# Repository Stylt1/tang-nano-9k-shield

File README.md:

<div align="center">

# Tang Nano 9K Shield

**A retro‑computing & I/O expansion board for the Sipeed Tang Nano 9K FPGA**

VGA · dual PS/2 · RP2040 co‑processor · USB‑C · Pmod · 16 DIP switches · SPI / I²C headers

</div>

---

## Table of contents

- [Overview](#overview)
- [Features](#features)
- [Gallery](#gallery)
- [Block diagram](#block-diagram)
- [Schematic](#schematic)
- [Hardware](#hardware)
  - [Power](#power)
  - [Video – VGA](#video--vga)
  - [Input – PS/2](#input--ps2)
  - [RP2040 co‑processor](#rp2040-co-processor)
  - [Pmod](#pmod)
  - [Headers](#headers)
- [Pin mapping](#pin-mapping)
- [PCB](#pcb)
  - [Layer stack](#layer-stack)
- [Getting started](#getting-started)
- [Repository structure](#repository-structure)
- [Status](#status)
- [License](#license)

---

## Overview

The **Tang Nano 9K Shield** turns the tiny Sipeed Tang Nano 9K into a small,
self‑contained retro computer / FPGA playground. The FPGA drives a **VGA monitor**
and reads two **PS/2 devices** (keyboard + mouse). An on‑board **RP2040** acts as a
co‑processor: it talks to the FPGA over SPI, reads **16 DIP switches**, and exposes
**USB‑C**, **I²C** and **SPI** to the outside world. A level‑shifted **Pmod** port lets
you plug in standard Digilent‑compatible modules.

The board runs from a **7.5–15 V DC barrel jack**, from **USB‑C**, or from the
**Tang Nano’s own USB**, all OR‑ed together with Schottky diodes.

## Features

| | |
|---|---|
| 🖥️ **VGA output** | DE‑15 connector, 4‑bit‑per‑channel resistor DAC (4096 colours), HSYNC / VSYNC |
| ⌨️ **2 × PS/2** | Stacked mini‑DIN 6 (keyboard + mouse), 5 V ↔ 3.3 V bidirectional level shifting |
| 🧠 **RP2040 co‑processor** | 133 MHz dual Cortex‑M0+, 4 MB QSPI flash, 12 MHz crystal, BOOT / RESET jumpers |
| 🔌 **USB‑C** | RP2040 native USB with ESD protection, VBUS detection and a switchable 5 V output (USB host mode) |
| 🎛️ **16 DIP switches** | 2 × 8‑way slide switches with pull‑ups, read by the RP2040 |
| 🧩 **Pmod port** | 2 × 6 right‑angle socket, 8 lines translated 1.8 V ↔ 3.3 V (TXS0108E) |
| 📡 **Expansion** | 7‑pin SPI header (CS + INT) and 4‑pin I²C header (4.7 kΩ pull‑ups) |
| ⚡ **Flexible power** | 7.5–15 V DC jack → 5 V synchronous buck, USB‑C, or Tang USB; on‑board 3.3 V and 1.8 V LDOs |
| 💡 **Status LEDs** | 5 V and 3.3 V power indicators |

## Gallery

### Renders

| Top | Bottom |
|:---:|:---:|
|  |  |
|  |  |

### KiCad 3D views

| Top | Bottom |
|:---:|:---:|
|  |  |

| VGA side | PS/2 side |
|:---:|:---:|
|  |  |

| DIP switches | Power & Pmod |
|:---:|:---:|
|  |  |

### Copper layers

| F.Cu – top · GND pour · main signals | In1.Cu – inner 1 · GND reference plane |
|:---:|:---:|
|  |  |

| In2.Cu – inner 2 · 3V3 pour · power & tertiary signals | B.Cu – bottom · GND pour · secondary signals |
|:---:|:---:|
|  |  |

<sub>Renders: KiCad 3D raytracer composited onto CC0 surface textures from <a href="https://polyhaven.com">Poly Haven</a>.</sub>

## Block diagram

<details>
<summary><b>Text version</b></summary>

```text
                    ┌──────────────────────────────┐
  DC 7.5–15 V ──►   │  TPS563201 buck  →  5V_BUCK  │──┐
                    └──────────────────────────────┘  │
  USB‑C VBUS ─────────────────────────────────────────┼──► 5 V rail ──► TLV75533 ─► 3V3 ──► TLV75518 ─► 1V8
  Tang 5 V   ◄────────────────────────────────────────┘    (Schottky OR‑ing)

 ┌───────────────────────┐   SPI (CS1 / INT1)   ┌─────────────────────────┐
 │                       │◄────────────────────►│        RP2040           │
 │   Tang Nano 9K        │                      │  W25Q32 flash, 12 MHz   │
 │   (Gowin GW1NR‑9)     │                      │                         │
 │                       │── RGB 4:4:4 + sync ──► VGA (DE‑15)              ├──► USB‑C (ESD, VBUS switch)
 │                       │◄─ 2 × CLK/DATA ──────► BSS138 ──► PS/2 × 2       ├──► 16 × DIP switch
 │                       │◄─ 8 lines @1.8 V ────► TXS0108E ──► Pmod (3.3 V)├──► I²C header
 │                       │◄─ SPI (CS2 / INT2) ──► SPI header               │
 └───────────────────────┘                      └─────────────────────────┘
```

</details>

Source: [`hardware/block_diagram.kicad_sch`](hardware/block_diagram.kicad_sch)

## Schematic

📄 Full-resolution PDF: [`docs/schematic.pdf`](docs/schematic.pdf) · Source: [`hardware/tang-nano-9k-shield.kicad_sch`](hardware/tang-nano-9k-shield.kicad_sch)

## Hardware

### Power

| Rail | Source | Part | Notes |
|---|---|---|---|
| **VIN** | DC barrel jack, **7.5–15 V, centre positive** | SS14 | Reverse‑polarity protection |
| **5V_BUCK** | VIN | TPS563201 | Synchronous buck, set to 5.07 V (56 k / 10 k divider) |
| **5V** | 5V_BUCK / USB‑C / Tang 5 V | 4 × SS14 | Diode OR‑ing of all three sources |
| **3V3** | 5V | TLV75533 | RP2040, logic, pull‑ups, Pmod VCC |
| **1V8** | 3V3 | TLV75518 | Side A of the Pmod level shifter (FPGA bank 3) |

> [!NOTE]
> The Tang Nano’s own 3.3 V pin is intentionally **not** used. The shield generates its own 3.3 V.

### Video – VGA

- 12 FPGA outputs → 4‑bit binary‑weighted resistor DAC per channel
  (**510 Ω / 1 kΩ / 2 kΩ / 3.9 kΩ**) → ~0.7 V full scale into the monitor’s 75 Ω.
- HSYNC / VSYNC through 100 Ω series resistors.
- 4096 colours (RGB 4:4:4).

### Input – PS/2

- Stacked dual mini‑DIN 6: **top = mouse (purple)**, **bottom = keyboard (green)**.
- Bidirectional open‑drain level shifting with **BSS138** MOSFETs (5 V ↔ 3.3 V),
  4.7 kΩ pull‑ups on both sides, 330 Ω series resistors on the connector side.

### RP2040 co‑processor

- RP2040 + **W25Q32JV** 4 MB QSPI flash + **12 MHz** crystal (Raspberry Pi reference design).
- **BOOT** and **RESET** solder jumpers for entering the USB bootloader.
- **USB‑C**: USBLC6‑2SC6 ESD protection, 27 Ω series resistors, 5.1 kΩ CC pull‑downs.
- **USB host power**: TPS2065C load switch can supply 5 V on VBUS (enable + fault signals on GPIO).
- **VBUS detect** through a 15 k / 20 k divider.

### Pmod

- Standard **Digilent Pmod™ 2 × 6** host socket (right‑angle, female).
- 8 signal lines driven from FPGA **bank 3 (1.8 V)** and translated to **3.3 V** by a **TXS0108E**.
- Pin 1 marked on the silkscreen, pinout table printed on the back of the board.

### Headers

| Header | Pins |
|---|---|
| **SPI** (J5) | GND · 3V3 · SCK · MOSI · MISO · CS · INT |
| **I²C** (J3) | GND · 3V3 · SDA · SCL |

## Pin mapping

<details>
<summary><b>FPGA (Tang Nano 9K) pins</b></summary>

| Function | FPGA pin(s) | I/O standard |
|---|---|---|
| VGA R0 · R1 · R2 · R3 | 57 · 56 · 55 · 54 | 3.3 V |
| VGA G0 · G1 · G2 · G3 | 53 · 51 · 42 · 41 | 3.3 V |
| VGA B0 · B1 · B2 · B3 | 35 · 40 · 34 · 33 | 3.3 V |
| VGA HSYNC · VSYNC | 30 · 29 | 3.3 V |
| PS/2 #1 CLK · DATA | 49 · 48 | 3.3 V |
| PS/2 #2 CLK · DATA | 32 · 31 | 3.3 V |
| SPI SCK · MOSI · MISO | 36 · 37 · 39 | 3.3 V |
| SPI CS1 · INT1 (RP2040) | 25 · 26 | 3.3 V |
| SPI CS2 · INT2 (header) | 27 · 28 | 3.3 V |
| Pmod 1 · 2 · 3 · 4 | 86 · 84 · 82 · 80 | **1.8 V** |
| Pmod 7 · 8 · 9 · 10 | 85 · 83 · 81 · 79 | **1.8 V** |

</details>

<details>
<summary><b>RP2040 GPIOs</b></summary>

| GPIO | Function |
|---|---|
| GPIO0 – GPIO15 | DIP switches SW1 – SW16 (active low, 10 kΩ pull‑up) |
| GPIO16 | SPI0 RX ← MOSI |
| GPIO17 | SPI0 CS ← CS1 |
| GPIO18 | SPI0 SCK |
| GPIO19 | SPI0 TX → MISO |
| GPIO20 | INT1 → FPGA |
| GPIO21 | USB_PWR_EN (TPS2065C enable) |
| GPIO22 | I²C1 SDA |
| GPIO23 | I²C1 SCL |
| GPIO24 | VBUS_DET |
| GPIO25 | USB_FLT (over‑current flag, active low) |
| GPIO26 – GPIO29 | free (ADC0 – ADC3) |

</details>

<details>
<summary><b>Pmod port (J8)</b></summary>

| Pmod pin | Signal | | Pmod pin | Signal |
|:---:|:---:|---|:---:|:---:|
| 1 | PMOD1 | | 7 | PMOD7 |
| 2 | PMOD2 | | 8 | PMOD8 |
| 3 | PMOD3 | | 9 | PMOD9 |
| 4 | PMOD4 | | 10 | PMOD10 |
| 5 | GND | | 11 | GND |
| 6 | 3V3 | | 12 | 3V3 |

</details>

## PCB

| | |
|---|---|
| **Size** | ~100 × 100 mm |
| **Layers** | 4 – F.Cu / In1.Cu / In2.Cu / B.Cu (see [Layer stack](#layer-stack)) |
| **Stackup** | JLCPCB JLC04161H‑7628, 1.6 mm, 1 oz outer / 0.5 oz inner |
| **Min. via** | 0.45 / 0.2 mm |
| **Components** | SMD 0603 / 0402 passives, SOT‑23, QFN‑56, TSSOP‑20 + THT connectors |
| **EDA** | KiCad 10 |

### Layer stack

| # | Layer | Copper pour (fill) | Routed on this layer |
|:---:|---|---|---|
| 1 | **F.Cu** (top) | GND | Main signals, component fan‑out |
| 2 | **In1.Cu** (inner 1) | GND – solid plane | Reference ground for the top‑layer signals |
| 3 | **In2.Cu** (inner 2) | 3V3 | Power distribution, tertiary signals |
| 4 | **B.Cu** (bottom) | GND | Secondary signals |

Images of each copper layer are in the [Gallery](#copper-layers).

Custom 3D models for the Tang Nano 9K, PS/2, VGA, DIP switches and DC jack are included in [`hardware/3dmodels/`](hardware/3dmodels).

## Getting started

### Ordering
Ready-to-upload files for JLCPCB are in [`production/v1.0/`](production/v1.0):

| File | Upload to JLCPCB as |
|---|---|
| `gerbers.zip` | Gerber files (Gerbers + Excellon drill) |
| `bom.csv` | BOM (with LCSC part numbers) |
| `cpl.csv` | CPL / pick & place |

1. Upload `gerbers.zip`, select **4 layers** and the **JLC04161H‑7628** stackup (1.6 mm).
2. For assembly, add `bom.csv` and `cpl.csv` and check part rotations in the JLC preview.

To regenerate the files, open `hardware/tang-nano-9k-shield.kicad_pro` in KiCad 10 and use **File → Fabrication Outputs**.

### Bring‑up
1. Power the board from a **current‑limited** supply on the DC jack, *without* the Tang Nano, and check **5 V, 3.3 V and 1.8 V**.
2. Connect USB‑C while bridging **BOOT**. The RP2040 should enumerate as **RPI‑RP2**.
3. Flash the RP2040 firmware, then plug in the Tang Nano 9K.
4. Load an FPGA bitstream (e.g. a VGA test pattern) using the pin mapping above.

> [!WARNING]
> Pmod lines are driven from the FPGA’s **1.8 V bank**. Set those pins to `LVCMOS18` in your constraints file.

## Repository structure

```text
tang-nano-9k-shield/
├── README.md
├── LICENSE
├── hardware/                          # KiCad 10 project
│   ├── tang-nano-9k-shield.kicad_pro
│   ├── tang-nano-9k-shield.kicad_sch  # Schematic
│   ├── tang-nano-9k-shield.kicad_pcb  # PCB layout
│   ├── block_diagram.kicad_pro
│   ├── block_diagram.kicad_sch        # Block diagram
│   └── 3dmodels/                      # Custom 3D models (VRML / STEP)
├── production/
│   └── v1.0/                          # JLCPCB fabrication outputs
│       ├── gerbers/                   # Gerbers + drill (unzipped)
│       ├── gerbers.zip
│       ├── bom.csv
│       └── cpl.csv
├── gateware/                          # FPGA designs for the Tang Nano 9K
│   └── constraints/                   # Gowin .cst pin constraints
├── CAD/                               # 3D models of the assembled board
│   ├── tang-nano-9k-shield.glb        # complete board with all parts (colours)
│   └── tang-nano-9k-shield.step       # for CAD – without parts that only have VRML models
├── datasheets/                        # INDEX.md with links to component datasheets
└── docs/
    ├── schematic.pdf
    └── images/
        ├── renders/                   # Renders and KiCad 3D views
        ├── layers/                    # Copper layer images
        ├── block-diagram.png
        └── schematic.png
```

## Status

- [x] Schematic
- [x] PCB layout & routing (DRC: 0 unconnected)
- [x] 3D models & renders
- [x] Fabrication outputs (Gerbers, BOM, CPL) – rev 1.0
- [ ] Prototype manufactured
- [ ] Hardware bring‑up
- [ ] RP2040 firmware
- [ ] FPGA example designs (VGA, PS/2, SPI bridge)

## License

© 2026 Stylt1. This project is licensed under [CC BY‑NC 4.0](https://creativecommons.org/licenses/by-nc/4.0/) – see [`LICENSE`](LICENSE).

---

<div align="center">
Made with ❤️ and KiCad
</div>

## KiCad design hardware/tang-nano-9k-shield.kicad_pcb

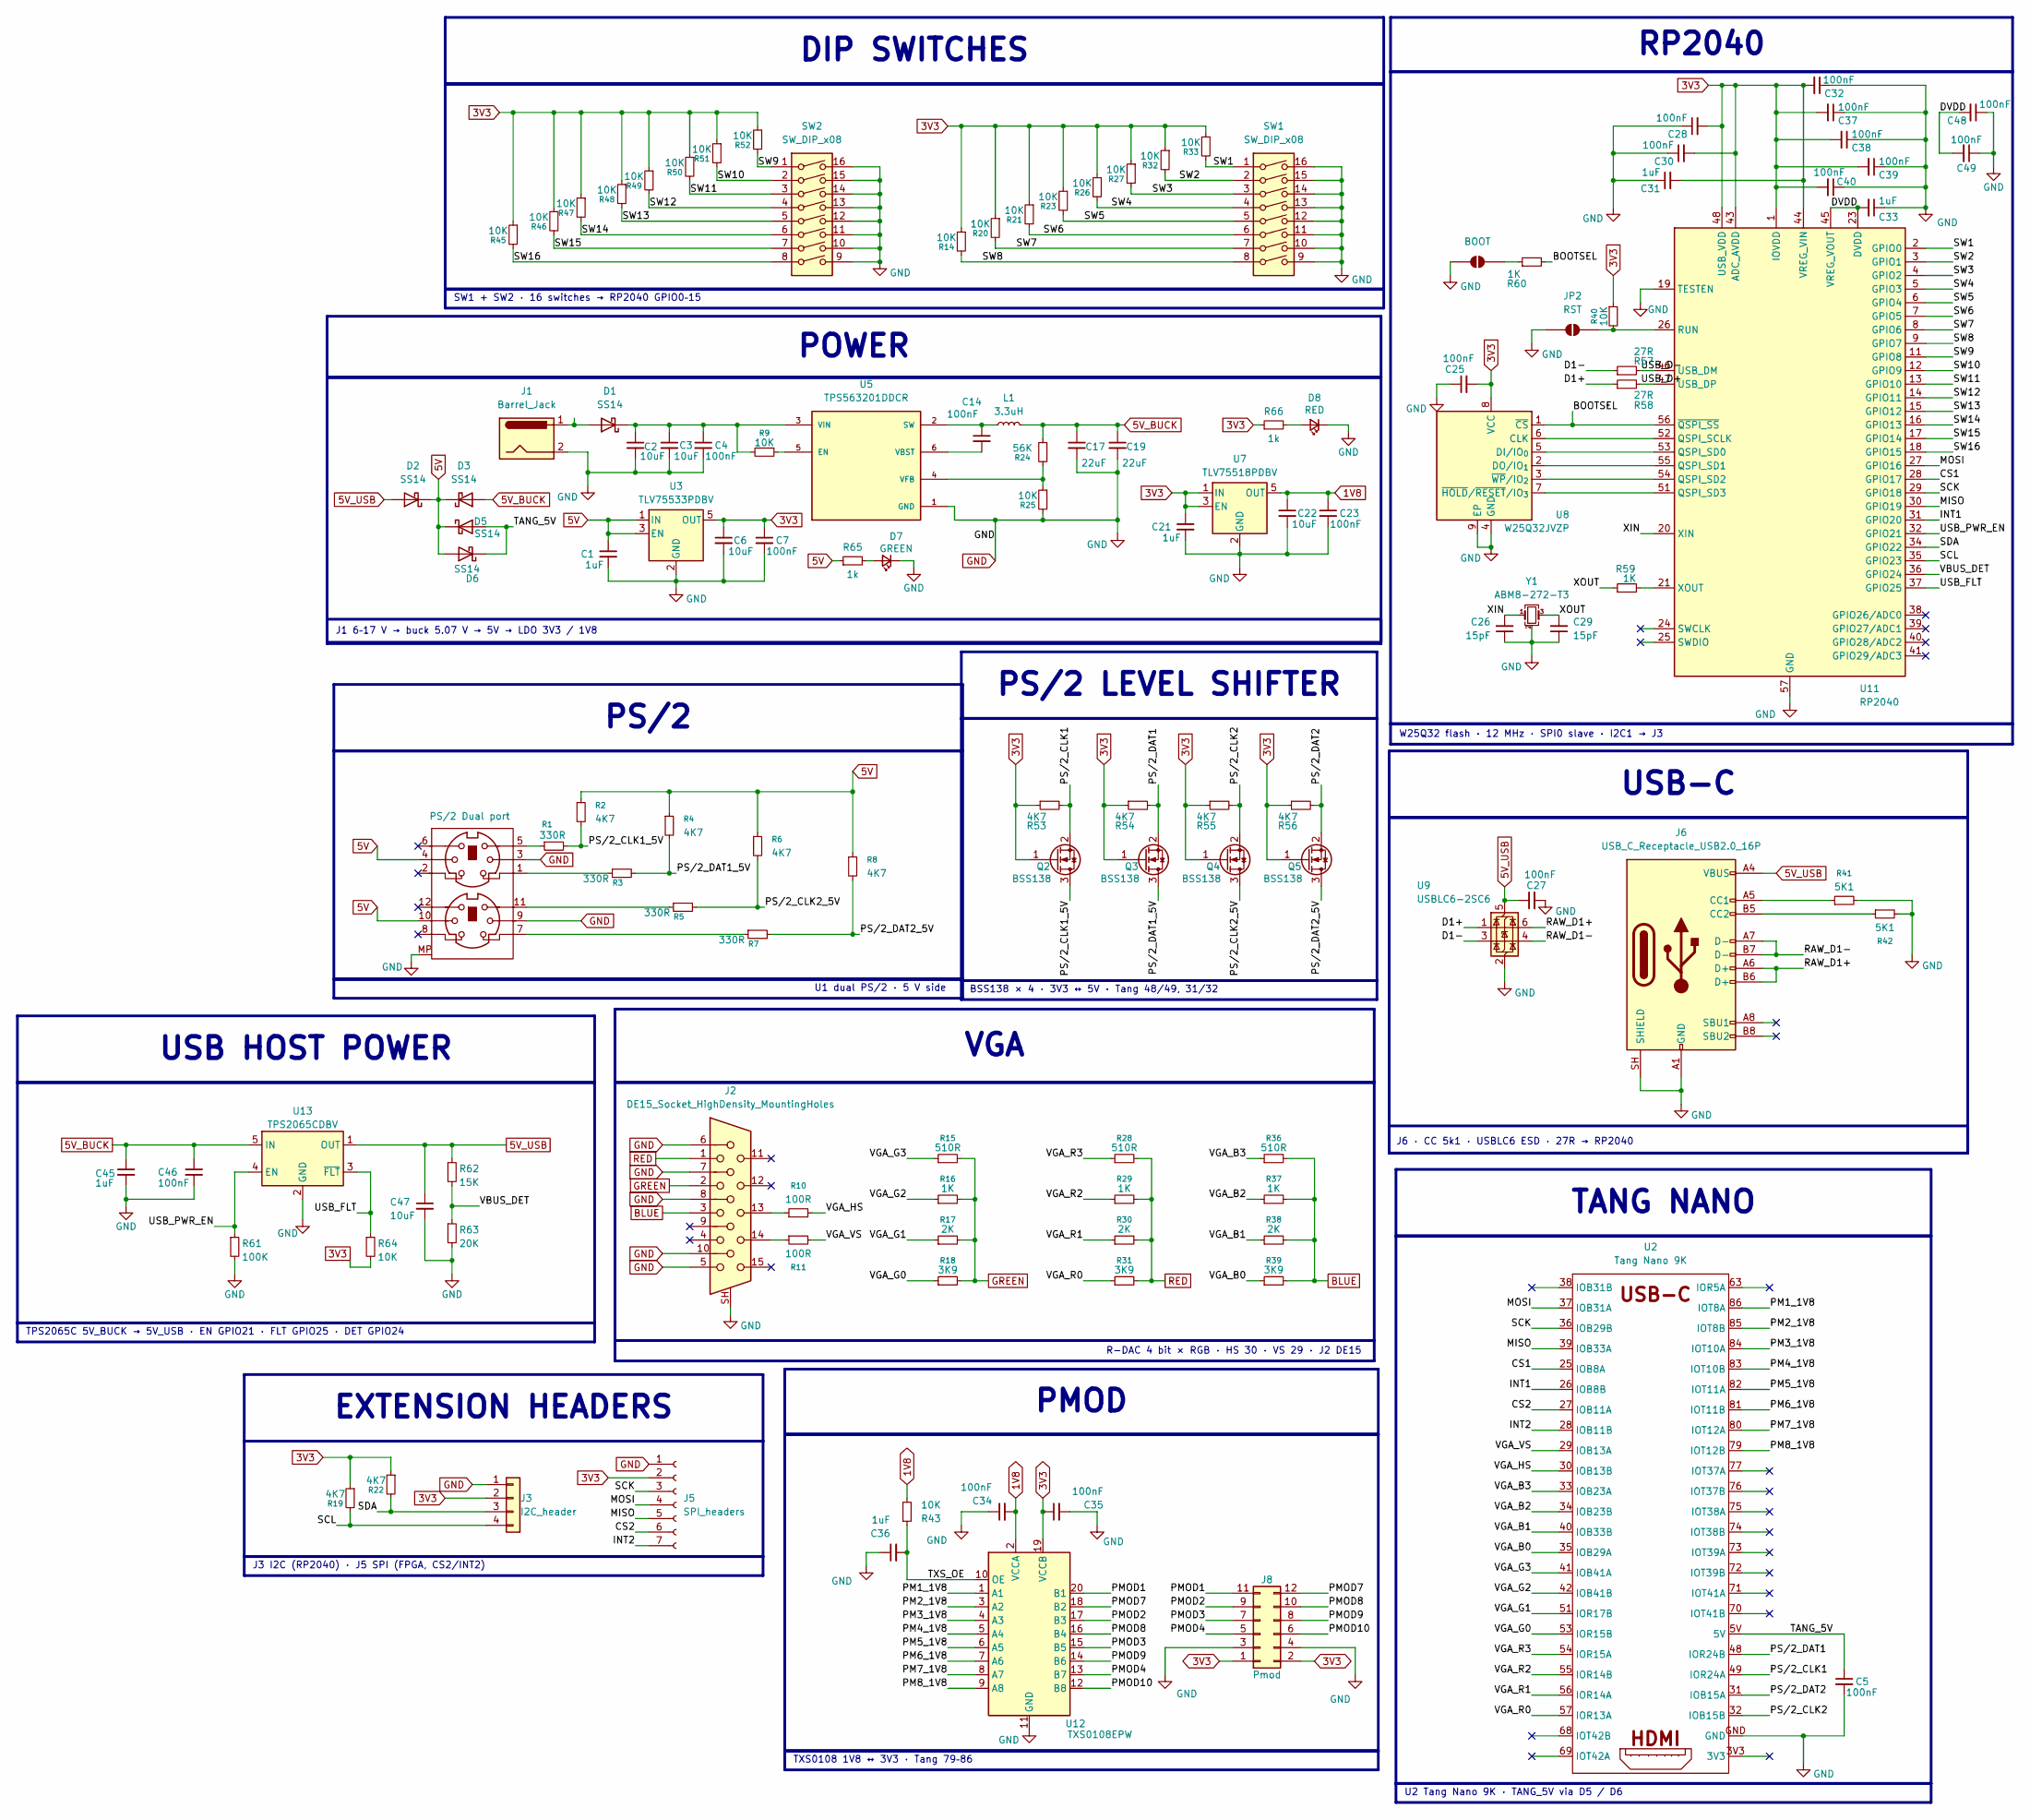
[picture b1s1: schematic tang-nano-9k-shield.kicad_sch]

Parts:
C1, C21, C36, C45: 1uF; C_0603_1608Metric; LCSC C15849
C2, C3, C6, C22, C47: 10uF; C_1206_3216Metric; LCSC C13585
C4, C5, C7, C14, C23, C25, C27, C32, C34, C35, C37, C38, C39, C40, C46: 100nF; C_0603_1608Metric; LCSC C14663
C17, C19: 22uF; C_1206_3216Metric; LCSC C12891
C26, C29: 15pF; C_0603_1608Metric; LCSC C1644
C28, C30, C48, C49: 100nF; C_0402_1005Metric; LCSC C1525
C31, C33: 1uF; C_0402_1005Metric; LCSC C52923
D1, D2, D3, D5, D6: SS14; D_SMA; LCSC C2480
D7: GREEN; LED_0805_2012Metric; LCSC C2297
D8: RED; LED_0603_1608Metric; LCSC C2286
J1: Barrel_Jack; BarrelJack_CLIFF_FC681465S_SMT_Horizontal
J2: DE15_Socket_HighDensity_MountingHoles; DSUB-15-HD_Socket_Horizontal_P2.29x2.54mm_EdgePinOffset8.35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
J3: I2C_header; PinHeader_1x04_P2.54mm_Vertical
J5: SPI_headers; PinHeader_1x07_P2.54mm_Vertical
J6: USB_C_Receptacle_USB2.0_16P; USB_C_Receptacle_G-Switch_GT-USB-7010ASV; LCSC C2988369
J8: Pmod; PinSocket_2x06_P2.54mm_Horizontal
JP1: BOOT; SolderJumper-2_P1.3mm_Open_TrianglePad1.0x1.5mm
JP2: RST; SolderJumper-2_P1.3mm_Open_TrianglePad1.0x1.5mm
L1: 3.3uH; L_Sunlord_SWPA6045S; MPN SWPA6045S3R3NT; LCSC C279943
Q2, Q3, Q4, Q5: BSS138; SOT-23; LCSC C7420339
R1, R3, R5, R7: 330R; R_0603_1608Metric; LCSC C23138
R2, R4, R6, R8, R19, R22, R53, R54, R55, R56: 4K7; R_0603_1608Metric; LCSC C23162
R9, R14, R20, R21, R23, R25, R26, R27, R32, R33, R40, R43, R45, R46, R47, R48, R49, R50, R51, R52, R64: 10K; R_0603_1608Metric; LCSC C25804
R10, R11: 100R; R_0603_1608Metric; LCSC C22775
R15, R28, R36: 510R; R_0603_1608Metric; LCSC C23193
R16, R29, R37, R59, R60: 1K; R_0603_1608Metric; LCSC C21190
R17, R30, R38: 2K; R_0603_1608Metric; LCSC C22975
R18, R31, R39: 3K9; R_0603_1608Metric; LCSC C23018
R24: 56K; R_0603_1608Metric; LCSC C23206
R41, R42: 5K1; R_0603_1608Metric; LCSC C23186
R57, R58: 27R; R_0603_1608Metric; LCSC C25190
R61: 100K; R_0603_1608Metric; LCSC C25803
R62: 15K; R_0603_1608Metric; LCSC C22809
R63: 20K; R_0603_1608Metric; LCSC C4184
R65, R66: 1k; R_0603_1608Metric; LCSC C21190
SW1, SW2: SW_DIP_x08; SW_DIP_SPSTx08_Slide_9.78x22.5mm_W7.62mm_P2.54mm
U1: PS/2 Dual port; PS-2_Dual_Stacked
U2: Tang Nano 9K; Tang-Nano-9K
U3: TLV75533PDBV; SOT-23-5; LCSC C404027
U5: TPS563201DDCR; SOT95P280X110-6N; PARTREV December 2015; LCSC C116592
U7: TLV75518PDBV; SOT-23-5; LCSC C2877863
U8: W25Q32JVZP; WSON-8-1EP_6x5mm_P1.27mm_EP3.4x4.3mm; LCSC C571260
U9: USBLC6-2SC6; SOT-23-6; LCSC C7519
U11: RP2040; QFN-56-1EP_7x7mm_P0.4mm_EP3.2x3.2mm; LCSC C2040
U12: TXS0108EPW; TSSOP-20_4.4x6.5mm_P0.65mm; LCSC C17206
U13: TPS2065CDBV; SOT-23-5; LCSC C353882
Y1: ABM8-272-T3; Crystal_SMD_3225-4Pin_3.2x2.5mm

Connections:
1V8: C22.1, C23.1, C34.2, R43.2, U7.5 (OUT), U12.2 (VCCA)
3V3: C6.1, C7.1, C21.1, C25.2, C28.2, C30.2, C31.2, C32.2, C35.1, C37.2, C38.2, C39.2, C40.2, J3.2, J5.2, J8.1, J8.2, Q2.1 (G), Q3.1 (G), Q4.1 (G), Q5.1 (G), R14.1, R19.1, R20.1, R21.1, R22.1, R23.1, R26.1, R27.1, R32.1, R33.1, R40.1, R45.1, R46.1, R47.1, R48.1, R49.1, R50.1, R51.1, R52.1, R53.1, R54.1, R55.1, R56.1, R64.2, R66.1, U3.5 (OUT), U7.1 (IN), U7.3 (EN), U8.8 (VCC), U11.1 (IOVDD), U11.10 (IOVDD), U11.22 (IOVDD), U11.33 (IOVDD), U11.42 (IOVDD), U11.43 (ADC_AVDD), U11.44 (VREG_VIN), U11.48 (USB_VDD), U11.49 (IOVDD), U12.19 (VCCB)
5V: C1.1, D2.1 (K), D3.1 (K), D5.1 (K), D6.2 (A), R2.1, R4.1, R6.1, R8.1, R65.1, U1.4, U1.10, U3.1 (IN), U3.3 (EN)
5V_BUCK: C17.1, C19.1, C45.1, C46.1, D3.2 (A), L1.2, R24.1, U13.5 (IN)
5V_USB: C27.1, C47.1, D2.2 (A), J6.A4 (VBUS), J6.A9 (VBUS), J6.B4 (VBUS), J6.B9 (VBUS), R62.1, U9.5 (VBUS), U13.1 (OUT)
/tang-nano-9k-shield/BOOTSEL: R60.2, U8.1 (~CS), U11.56 (~QSPI_SS)
/tang-nano-9k-shield/CS1: U2.25 (IOB8A), U11.28 (GPIO17)
/tang-nano-9k-shield/CS2: J5.6, U2.27 (IOB11A)
/tang-nano-9k-shield/D1+: R58.1, U9.1 (I/O1)
/tang-nano-9k-shield/D1-: R57.1, U9.3 (I/O2)
/tang-nano-9k-shield/DVDD: C33.2, C48.2, C49.2, U11.23 (DVDD), U11.45 (VREG_VOUT), U11.50 (DVDD)
/tang-nano-9k-shield/INT1: U2.26 (IOB8B), U11.31 (GPIO20)
/tang-nano-9k-shield/INT2: J5.7, U2.28 (IOB11B)
/tang-nano-9k-shield/MISO: J5.5, U2.39 (IOB33A), U11.30 (GPIO19)
/tang-nano-9k-shield/MOSI: J5.4, U2.37 (IOB31A), U11.27 (GPIO16)
/tang-nano-9k-shield/PM1_1V8: U2.86 (IOT8A), U12.1 (A1)
/tang-nano-9k-shield/PM2_1V8: U2.85 (IOT8B), U12.3 (A2)
/tang-nano-9k-shield/PM3_1V8: U2.84 (IOT10A), U12.4 (A3)
/tang-nano-9k-shield/PM4_1V8: U2.83 (IOT10B), U12.5 (A4)
/tang-nano-9k-shield/PM5_1V8: U2.82 (IOT11A), U12.6 (A5)
/tang-nano-9k-shield/PM6_1V8: U2.81 (IOT11B), U12.7 (A6)
/tang-nano-9k-shield/PM7_1V8: U2.80 (IOT12A), U12.8 (A7)
/tang-nano-9k-shield/PM8_1V8: U2.79 (IOT12B), U12.9 (A8)
/tang-nano-9k-shield/PMOD1: J8.11, U12.20 (B1)
/tang-nano-9k-shield/PMOD2: J8.9, U12.17 (B3)
/tang-nano-9k-shield/PMOD3: J8.7, U12.15 (B5)
/tang-nano-9k-shield/PMOD4: J8.5, U12.13 (B7)
/tang-nano-9k-shield/PMOD7: J8.12, U12.18 (B2)
/tang-nano-9k-shield/PMOD8: J8.10, U12.16 (B4)
/tang-nano-9k-shield/PMOD9: J8.8, U12.14 (B6)
/tang-nano-9k-shield/PMOD10: J8.6, U12.12 (B8)
/tang-nano-9k-shield/PS/2_CLK1: Q2.2 (S), R53.2, U2.49 (IOR24A)
/tang-nano-9k-shield/PS/2_CLK1_5V: Q2.3 (D), R1.2, R2.2
/tang-nano-9k-shield/PS/2_CLK2: Q4.2 (S), R55.2, U2.32 (IOB15B)
/tang-nano-9k-shield/PS/2_CLK2_5V: Q4.3 (D), R5.2, R6.2
/tang-nano-9k-shield/PS/2_DAT1: Q3.2 (S), R54.2, U2.48 (IOR24B)
/tang-nano-9k-shield/PS/2_DAT1_5V: Q3.3 (D), R3.2, R4.2
/tang-nano-9k-shield/PS/2_DAT2: Q5.2 (S), R56.2, U2.31 (IOB15A)
/tang-nano-9k-shield/PS/2_DAT2_5V: Q5.3 (D), R7.2, R8.2
/tang-nano-9k-shield/RAW_D1+: J6.A6 (D+), J6.B6 (D+), U9.6 (I/O1)
/tang-nano-9k-shield/RAW_D1-: J6.A7 (D-), J6.B7 (D-), U9.4 (I/O2)
/tang-nano-9k-shield/SCK: J5.3, U2.36 (IOB29B), U11.29 (GPIO18)
/tang-nano-9k-shield/SCL: J3.4, R19.2, U11.35 (GPIO23)
/tang-nano-9k-shield/SDA: J3.3, R22.2, U11.34 (GPIO22)
/tang-nano-9k-shield/SW1: R33.2, SW1.1, U11.2 (GPIO0)
/tang-nano-9k-shield/SW2: R32.2, SW1.2, U11.3 (GPIO1)
/tang-nano-9k-shield/SW3: R27.2, SW1.3, U11.4 (GPIO2)
/tang-nano-9k-shield/SW4: R26.2, SW1.4, U11.5 (GPIO3)
/tang-nano-9k-shield/SW5: R23.2, SW1.5, U11.6 (GPIO4)
/tang-nano-9k-shield/SW6: R21.2, SW1.6, U11.7 (GPIO5)
/tang-nano-9k-shield/SW7: R20.2, SW1.7, U11.8 (GPIO6)
/tang-nano-9k-shield/SW8: R14.2, SW1.8, U11.9 (GPIO7)
/tang-nano-9k-shield/SW9: R52.2, SW2.1, U11.11 (GPIO8)
/tang-nano-9k-shield/SW10: R51.2, SW2.2, U11.12 (GPIO9)
/tang-nano-9k-shield/SW11: R50.2, SW2.3, U11.13 (GPIO10)
/tang-nano-9k-shield/SW12: R49.2, SW2.4, U11.14 (GPIO11)
/tang-nano-9k-shield/SW13: R48.2, SW2.5, U11.15 (GPIO12)
/tang-nano-9k-shield/SW14: R47.2, SW2.6, U11.16 (GPIO13)
/tang-nano-9k-shield/SW15: R46.2, SW2.7, U11.17 (GPIO14)
/tang-nano-9k-shield/SW16: R45.2, SW2.8, U11.18 (GPIO15)
/tang-nano-9k-shield/TANG_5V: C5.1, D5.2 (A), D6.1 (K), U2.5V
/tang-nano-9k-shield/TXS_OE: C36.2, R43.1, U12.10 (OE)
/tang-nano-9k-shield/USB_D+: R58.2, U11.47 (USB_DP)
/tang-nano-9k-shield/USB_D-: R57.2, U11.46 (USB_DM)
/tang-nano-9k-shield/USB_FLT: R64.1, U11.37 (GPIO25), U13.3 (~FLT)
/tang-nano-9k-shield/USB_PWR_EN: R61.1, U11.32 (GPIO21), U13.4 (EN)
/tang-nano-9k-shield/VBUS_DET: R62.2, R63.1, U11.36 (GPIO24)
/tang-nano-9k-shield/VGA_B0: R39.1, U2.35 (IOB29A)
/tang-nano-9k-shield/VGA_B1: R38.1, U2.40 (IOB33B)
/tang-nano-9k-shield/VGA_B2: R37.1, U2.34 (IOB23B)
/tang-nano-9k-shield/VGA_B3: R36.1, U2.33 (IOB23A)
/tang-nano-9k-shield/VGA_G0: R18.1, U2.53 (IOR15B)
/tang-nano-9k-shield/VGA_G1: R17.1, U2.51 (IOR17B)
/tang-nano-9k-shield/VGA_G2: R16.1, U2.42 (IOB41B)
/tang-nano-9k-shield/VGA_G3: R15.1, U2.41 (IOB41A)
/tang-nano-9k-shield/VGA_HS: R10.2, U2.30 (IOB13B)
/tang-nano-9k-shield/VGA_R0: R31.1, U2.57 (IOR13A)
/tang-nano-9k-shield/VGA_R1: R30.1, U2.56 (IOR14A)
/tang-nano-9k-shield/VGA_R2: R29.1, U2.55 (IOR14B)
/tang-nano-9k-shield/VGA_R3: R28.1, U2.54 (IOR15A)
/tang-nano-9k-shield/VGA_VS: R11.2, U2.29 (IOB13A)
/tang-nano-9k-shield/XIN: C26.2, U11.20 (XIN), Y1.1
/tang-nano-9k-shield/XOUT: C29.2, R59.1, Y1.3
BLUE: J2.3, R36.2, R37.2, R38.2, R39.2
GND: C1.2, C2.2, C3.2, C4.2, C5.2, C6.2, C7.2, C17.2, C19.2, C21.2, C22.2, C23.2, C25.1, C26.1, C27.2, C28.1, C29.1, C30.1, C31.1, C32.1, C33.1, C34.1, C35.2, C36.1, C37.1, C38.1, C39.1, C40.1, C45.2, C46.2, C47.2, C48.1, C49.1, D7.1 (K), D8.1 (K), J1.2, J2.5, J2.6, J2.7, J2.8, J2.10, J2.SH, J3.1, J5.1, J6.A1 (GND), J6.A12 (GND), J6.B1 (GND), J6.B12 (GND), J6.SH (SHIELD), J8.3, J8.4, JP1.1 (A), JP2.1 (A), R25.2, R41.2, R42.2, R61.2, R63.2, SW1.9, SW1.10, SW1.11, SW1.12, SW1.13, SW1.14, SW1.15, SW1.16, SW2.9, SW2.10, SW2.11, SW2.12, SW2.13, SW2.14, SW2.15, SW2.16, U1.3, U1.9, U1.MP, U2.GND, U3.2 (GND), U5.1 (GND), U7.2 (GND), U8.4 (GND), U8.9 (EP), U9.2 (GND), U11.19 (TESTEN), U11.57 (GND), U12.11 (GND), U13.2 (GND), Y1.2 (G), Y1.4 (G); also elsewhere on the board
GREEN: J2.2, R15.2, R16.2, R17.2, R18.2
unnamed: D1.2 (A), J1.1
unnamed: C2.1, C3.1, C4.1, D1.1 (K), R9.2, U5.3 (VIN)
unnamed 88: D7.2 (A), R65.2; also elsewhere on the board
unnamed 89: D8.2 (A), R66.2; also elsewhere on the board
unnamed: J2.13, R10.1
unnamed: J2.14, R11.1
unnamed: J6.A5 (CC1), R41.1
unnamed: J6.B5 (CC2), R42.1
unnamed 94: JP1.2 (B), R60.1; also elsewhere on the board
unnamed 95: JP2.2 (B), R40.2, U11.26 (RUN); also elsewhere on the board
unnamed: R1.1, U1.5
unnamed: R3.1, U1.1
unnamed: R5.1, U1.11
unnamed: R7.1, U1.7
unnamed: R9.1, U5.5 (EN)
unnamed: C14.1, L1.1, U5.2 (SW)
unnamed: C14.2, U5.6 (VBST)
unnamed: R24.2, R25.1, U5.4 (VFB)
unnamed: U8.6 (CLK), U11.52 (QSPI_SCLK)
unnamed: U8.5 (DI/IO_{0}), U11.53 (QSPI_SD0)
unnamed: U8.2 (DO/IO_{1}), U11.55 (QSPI_SD1)
unnamed: U8.3 (~WP/IO_{2}), U11.54 (QSPI_SD2)
unnamed: U8.7 (~HOLD/~RESET/IO_{3}), U11.51 (QSPI_SD3)
unnamed: R59.2, U11.21 (XOUT)
RED: J2.1, R28.2, R29.2, R30.2, R31.2

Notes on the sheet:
J6 · CC 5k1 · USBLC6 ESD · 27R → RP2040
PMOD
DIP SWITCHES
TPS2065C 5V_BUCK → 5V_USB · EN GPIO21 · FLT GPIO25 · DET GPIO24
EXTENSION HEADERS
USB HOST POWER
U1 dual PS/2 · 5 V side
SW1 + SW2 · 16 switches → RP2040 GPIO0–15
PS/2
J3 I2C (RP2040) · J5 SPI (FPGA, CS2/INT2)
R-DAC 4 bit × RGB · HS 30 · VS 29 · J2 DE15
RP2040
USB-C
POWER
TANG NANO
VGA
TXS0108 1V8 ↔ 3V3 · Tang 79–86
BSS138 × 4 · 3V3 ↔ 5V · Tang 48/49, 31/32
U2 Tang Nano 9K · TANG_5V via D5 / D6
PS/2 LEVEL SHIFTER
J1 6–17 V → buck 5.07 V → 5V → LDO 3V3 / 1V8
W25Q32 flash · 12 MHz · SPI0 slave · I2C1 → J3

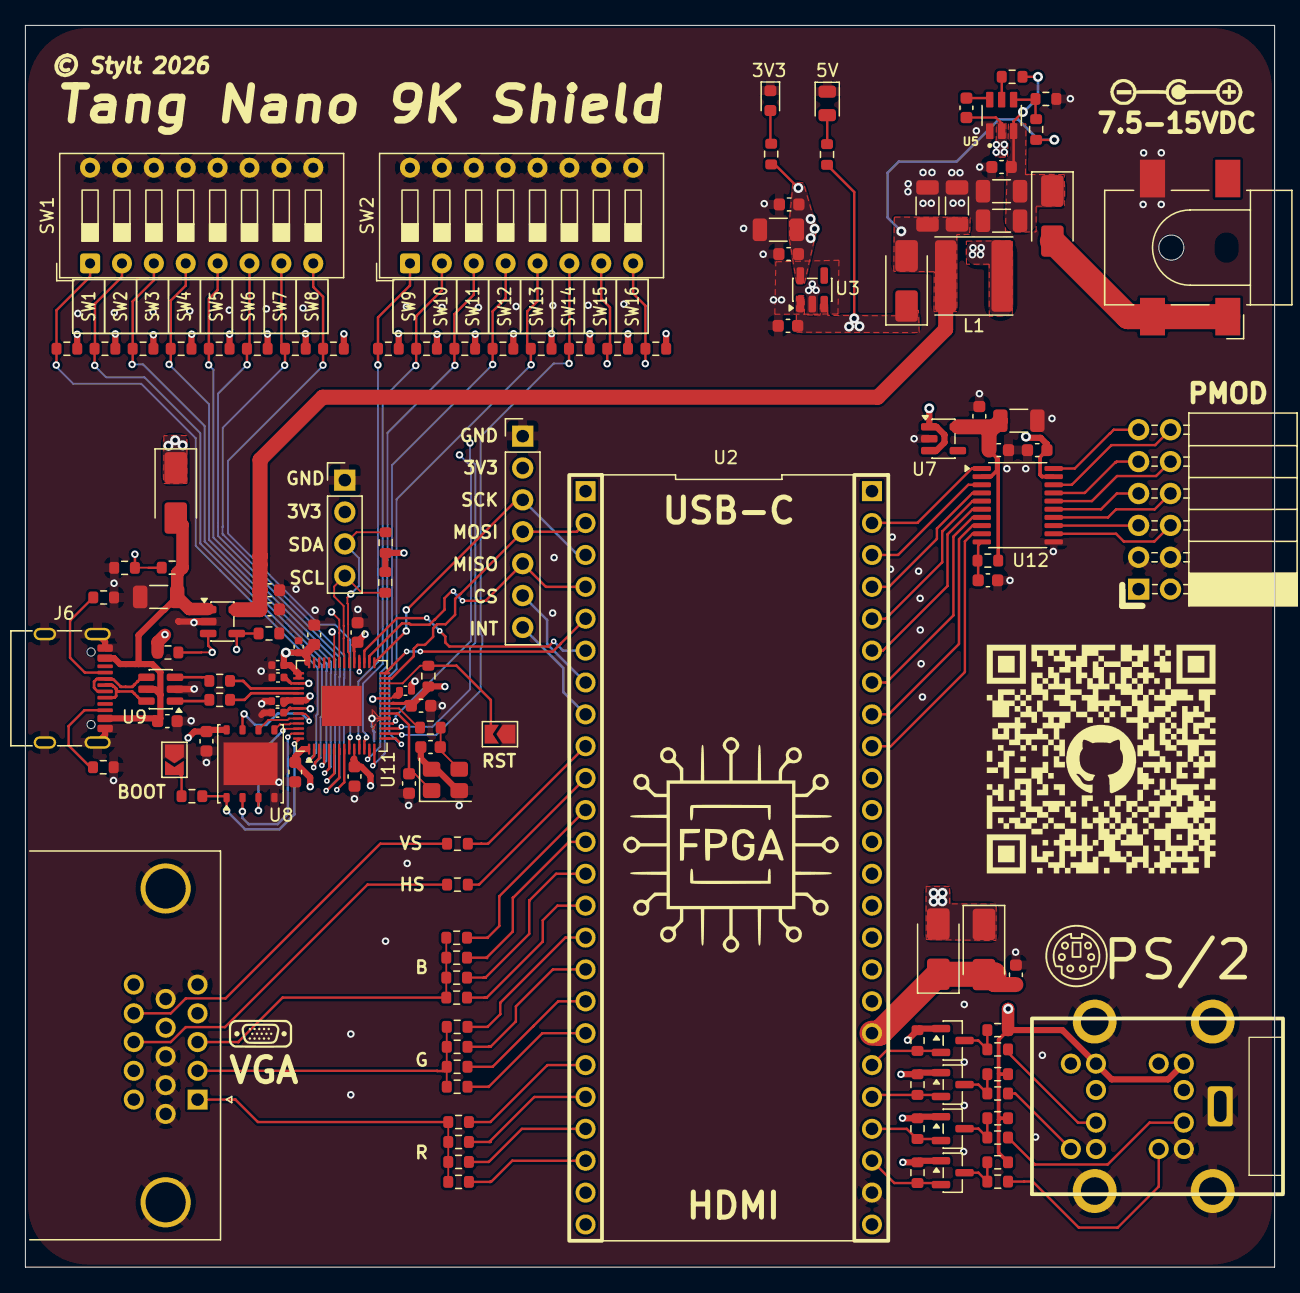
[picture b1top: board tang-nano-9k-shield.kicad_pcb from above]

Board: 4 copper layers, 99.5 x 98.9 mm, 128 parts (0 on the bottom side), 111 nets.

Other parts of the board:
3V3: RED; LED_0603_1608Metric
5V: GREEN; LED_0805_2012Metric
BOOT: BOOT; SolderJumper-2_P1.3mm_Open_TrianglePad1.0x1.5mm
RST: RST; SolderJumper-2_P1.3mm_Open_TrianglePad1.0x1.5mm

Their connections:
GND: 3V3.1 (K), 5V.1 (K), BOOT.1 (A), RST.1 (A); also elsewhere on the board
unnamed 88: 5V.2 (A); also elsewhere on the board
unnamed 89: 3V3.2 (A); also elsewhere on the board
unnamed 94: BOOT.2 (B); also elsewhere on the board
unnamed 95: RST.2 (B); also elsewhere on the board

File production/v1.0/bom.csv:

Comment,Designator,Footprint,LCSC Part #,Quantity
RED,3V3,LED_0603_1608Metric,C2286,1
GREEN,5V,LED_0805_2012Metric,C2297,1
1uF,"C1,C21,C36,C45",C_0603_1608Metric,C15849,4
10uF,"C2,C3,C6,C22,C47",C_1206_3216Metric,C13585,5
100nF,"C4,C5,C7,C14,C23,C25,C27,C32,C34,C35,C37,C38,C39,C40,C46",C_0603_1608Metric,C14663,15
22uF,"C17,C19",C_1206_3216Metric,C12891,2
15pF,"C26,C29",C_0603_1608Metric,C1644,2
100nF,"C28,C30,C48,C49",C_0402_1005Metric,C1525,4
1uF,"C31,C33",C_0402_1005Metric,C52923,2
SS14,"D1,D2,D3,D5,D6",D_SMA,C2480,5
Barrel_Jack,J1,BarrelJack_CLIFF_FC681465S_SMT_Horizontal,,1
DE15_Socket_HighDensity_MountingHoles,J2,DSUB-15-HD_Socket_Horizontal_P2.29x2.54mm_EdgePinOffset8.35mm_Housed_MountingHolesOffset10.89mm,,1
I2C_header,J3,PinHeader_1x04_P2.54mm_Vertical,,1
SPI_headers,J5,PinHeader_1x07_P2.54mm_Vertical,,1
USB_C_Receptacle_USB2.0_16P,J6,USB_C_Receptacle_G-Switch_GT-USB-7010ASV,C2988369,1
Pmod,J8,PinSocket_2x06_P2.54mm_Horizontal,,1
3.3uH,L1,L_Sunlord_SWPA6045S,C279943,1
BSS138,"Q2,Q3,Q4,Q5",SOT-23,C7420339,4
330R,"R1,R3,R5,R7",R_0603_1608Metric,C23138,4
4K7,"R2,R4,R6,R8,R19,R22,R53,R54,R55,R56",R_0603_1608Metric,C23162,10
10K,"R9,R14,R20,R21,R23,R25,R26,R27,R32,R33,R40,R43,R45,R46,R47,R48,R49,R50,R51,R52,R64",R_0603_1608Metric,C25804,21
100R,"R10,R11",R_0603_1608Metric,C22775,2
510R,"R15,R28,R36",R_0603_1608Metric,C23193,3
1K,"R16,R29,R37,R59,R60",R_0603_1608Metric,C21190,5
2K,"R17,R30,R38",R_0603_1608Metric,C22975,3
3K9,"R18,R31,R39",R_0603_1608Metric,C23018,3
56K,R24,R_0603_1608Metric,C23206,1
5K1,"R41,R42",R_0603_1608Metric,C23186,2
27R,"R57,R58",R_0603_1608Metric,C25190,2
100K,R61,R_0603_1608Metric,C25803,1
15K,R62,R_0603_1608Metric,C22809,1
20K,R63,R_0603_1608Metric,C4184,1
1k,"R65,R66",R_0603_1608Metric,C21190,2
SW_DIP_x08,"SW1,SW2",SW_DIP_SPSTx08_Slide_9.78x22.5mm_W7.62mm_P2.54mm,,2
PS/2 Dual port,U1,PS-2_Dual_Stacked,,1
Tang Nano 9K,U2,Tang-Nano-9K,,1
TLV75533PDBV,U3,SOT-23-5,C404027,1
TPS563201DDCR,U5,SOT95P280X110-6N,C116592,1
TLV75518PDBV,U7,SOT-23-5,C2877863,1
W25Q32JVZP,U8,WSON-8-1EP_6x5mm_P1.27mm_EP3.4x4.3mm,C571260,1
USBLC6-2SC6,U9,SOT-23-6,C7519,1
RP2040,U11,QFN-56-1EP_7x7mm_P0.4mm_EP3.2x3.2mm,C2040,1
TXS0108EPW,U12,TSSOP-20_4.4x6.5mm_P0.65mm,C17206,1
TPS2065CDBV,U13,SOT-23-5,C353882,1
ABM8-272-T3,Y1,Crystal_SMD_3225-4Pin_3.2x2.5mm,,1

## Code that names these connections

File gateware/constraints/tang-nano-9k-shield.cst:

// =============================================================================
// Tang Nano 9K Shield – physical constraints (Gowin GW1NR-9, QN88P)
// =============================================================================
// Pin numbers verified against:
//   - hardware/tang-nano-9k-shield.kicad_sch (U2 pin -> net label)
//   - hardware/tang-nano-9k-shield.kicad_pcb (U2 pad -> net, U12/J8 for Pmod)
//   - Sipeed Tang Nano 9K schematic 3674 (2024-03-11): bank voltages,
//     clock, LEDs, buttons, HDMI, SD card
//
// Bank voltages on the Tang Nano 9K:
//   VCCO0/1/2 = 3.3 V -> LVCMOS33 (VGA, PS/2, SPI, clock)
//   VCCO3     = 1.8 V -> LVCMOS18 (Pmod 79-86, LEDs, buttons)
//
// Comment out any port your design does not use – Gowin reports an error
// for constraints on ports that do not exist in the top module.
// =============================================================================


// ---------------------------------------------------------------------------
// Onboard Tang Nano 9K resources
// ---------------------------------------------------------------------------

// 27 MHz crystal oscillator
IO_LOC  "clk" 52;
IO_PORT "clk" IO_TYPE=LVCMOS33 PULL_MODE=UP;

// 6 orange LEDs, active LOW (anode on VCCO3_1V8)
IO_LOC  "led[0]" 10;
IO_LOC  "led[1]" 11;
IO_LOC  "led[2]" 13;
IO_LOC  "led[3]" 14;
IO_LOC  "led[4]" 15;
IO_LOC  "led[5]" 16;
IO_PORT "led[0]" IO_TYPE=LVCMOS18 PULL_MODE=UP DRIVE=8;
IO_PORT "led[1]" IO_TYPE=LVCMOS18 PULL_MODE=UP DRIVE=8;
IO_PORT "led[2]" IO_TYPE=LVCMOS18 PULL_MODE=UP DRIVE=8;
IO_PORT "led[3]" IO_TYPE=LVCMOS18 PULL_MODE=UP DRIVE=8;
IO_PORT "led[4]" IO_TYPE=LVCMOS18 PULL_MODE=UP DRIVE=8;
IO_PORT "led[5]" IO_TYPE=LVCMOS18 PULL_MODE=UP DRIVE=8;

// 2 push buttons, active LOW (10k pull-up to VCCO3_1V8 on the Tang)
// Pin 4 is also JTAG_SEL: to use it as GPIO enable
// Project -> Configuration -> Dual-Purpose Pin -> "Use JTAG as regular IO".
IO_LOC  "btn[0]" 3;     // Tang net PIN3_IOT2A_BUTTON_S1
IO_LOC  "btn[1]" 4;     // Tang net PIN4_IOL5A_JTAG_SEL_S2
IO_PORT "btn[0]" IO_TYPE=LVCMOS18 PULL_MODE=NONE;
IO_PORT "btn[1]" IO_TYPE=LVCMOS18 PULL_MODE=NONE;


// ---------------------------------------------------------------------------
// VGA (J2, DE-15) – 4-bit R-2R-style resistor DAC per channel (RGB444)
// Bit 0 = LSB (3.9k), bit 3 = MSB (510R)
// ---------------------------------------------------------------------------
IO_LOC  "vga_r[0]" 57;
IO_LOC  "vga_r[1]" 56;
IO_LOC  "vga_r[2]" 55;
IO_LOC  "vga_r[3]" 54;
IO_LOC  "vga_g[0]" 53;
IO_LOC  "vga_g[1]" 51;
IO_LOC  "vga_g[2]" 42;
IO_LOC  "vga_g[3]" 41;
IO_LOC  "vga_b[0]" 35;
IO_LOC  "vga_b[1]" 40;
IO_LOC  "vga_b[2]" 34;
IO_LOC  "vga_b[3]" 33;
IO_LOC  "vga_hs"   30;
IO_LOC  "vga_vs"   29;

IO_PORT "vga_r[0]" IO_TYPE=LVCMOS33 PULL_MODE=NONE DRIVE=8;
IO_PORT "vga_r[1]" IO_TYPE=LVCMOS33 PULL_MODE=NONE DRIVE=8;
IO_PORT "vga_r[2]" IO_TYPE=LVCMOS33 PULL_MODE=NONE DRIVE=8;
IO_PORT "vga_r[3]" IO_TYPE=LVCMOS33 PULL_MODE=NONE DRIVE=8;
IO_PORT "vga_g[0]" IO_TYPE=LVCMOS33 PULL_MODE=NONE DRIVE=8;
IO_PORT "vga_g[1]" IO_TYPE=LVCMOS33 PULL_MODE=NONE DRIVE=8;
IO_PORT "vga_g[2]" IO_TYPE=LVCMOS33 PULL_MODE=NONE DRIVE=8;
IO_PORT "vga_g[3]" IO_TYPE=LVCMOS33 PULL_MODE=NONE DRIVE=8;
IO_PORT "vga_b[0]" IO_TYPE=LVCMOS33 PULL_MODE=NONE DRIVE=8;
IO_PORT "vga_b[1]" IO_TYPE=LVCMOS33 PULL_MODE=NONE DRIVE=8;
IO_PORT "vga_b[2]" IO_TYPE=LVCMOS33 PULL_MODE=NONE DRIVE=8;
IO_PORT "vga_b[3]" IO_TYPE=LVCMOS33 PULL_MODE=NONE DRIVE=8;
IO_PORT "vga_hs"   IO_TYPE=LVCMOS33 PULL_MODE=NONE DRIVE=8;
IO_PORT "vga_vs"   IO_TYPE=LVCMOS33 PULL_MODE=NONE DRIVE=8;


// ---------------------------------------------------------------------------
// PS/2 (U1, stacked mini-DIN 6) via BSS138 level shifters to 5 V
// External 4.7k pull-ups on both sides -> no internal pull.
// Drive as open-drain in HDL:  assign ps2_clk[n] = drive_low ? 1'b0 : 1'bz;
//   index 0 = PS/2 #1 (U1 pins 1-6), index 1 = PS/2 #2 (U1 pins 7-12)
// ---------------------------------------------------------------------------
IO_LOC  "ps2_clk[0]" 49;
IO_LOC  "ps2_dat[0]" 48;
IO_LOC  "ps2_clk[1]" 32;
IO_LOC  "ps2_dat[1]" 31;
IO_PORT "ps2_clk[0]" IO_TYPE=LVCMOS33 PULL_MODE=NONE;
IO_PORT "ps2_dat[0]" IO_TYPE=LVCMOS33 PULL_MODE=NONE;
IO_PORT "ps2_clk[1]" IO_TYPE=LVCMOS33 PULL_MODE=NONE;
IO_PORT "ps2_dat[1]" IO_TYPE=LVCMOS33 PULL_MODE=NONE;


// ---------------------------------------------------------------------------
// SPI bus – FPGA is master
// Shared by: RP2040 (CS1/INT1), SPI header J5 (CS2/INT2) and the Tang's
// onboard microSD slot (SD CS = pin 38). Keep every unused CS HIGH.
// ---------------------------------------------------------------------------
IO_LOC  "spi_sck"  36;
IO_LOC  "spi_mosi" 37;
IO_LOC  "spi_miso" 39;
IO_LOC  "spi_cs1"  25;   // -> RP2040 (GPIO17, SPI0 CSn)
IO_LOC  "spi_int1" 26;   // <- RP2040 (GPIO20)
IO_LOC  "spi_cs2"  27;   // -> SPI header J5 pin 6
IO_LOC  "spi_int2" 28;   // <- SPI header J5 pin 7
IO_LOC  "sd_cs"    38;   // -> Tang onboard microSD (not routed on the shield)

IO_PORT "spi_sck"  IO_TYPE=LVCMOS33 PULL_MODE=NONE DRIVE=8;
IO_PORT "spi_mosi" IO_TYPE=LVCMOS33 PULL_MODE=NONE DRIVE=8;
IO_PORT "spi_miso" IO_TYPE=LVCMOS33 PULL_MODE=UP;
IO_PORT "spi_cs1"  IO_TYPE=LVCMOS33 PULL_MODE=UP DRIVE=8;
IO_PORT "spi_int1" IO_TYPE=LVCMOS33 PULL_MODE=UP;
IO_PORT "spi_cs2"  IO_TYPE=LVCMOS33 PULL_MODE=UP DRIVE=8;
IO_PORT "spi_int2" IO_TYPE=LVCMOS33 PULL_MODE=UP;
IO_PORT "sd_cs"    IO_TYPE=LVCMOS33 PULL_MODE=UP DRIVE=8;


// ---------------------------------------------------------------------------
// Pmod (J8, 2x6) via TXS0108E: FPGA side 1.8 V, Pmod side 3.3 V
// No internal pulls – they fight the TXS0108E one-shot edge accelerators.
// Index = Digilent Pmod pin number (1-4 top row, 7-10 bottom row).
// Pin 86 is also BL_PWM for the Tang's LCD connector – leave the LCD unplugged.
// ---------------------------------------------------------------------------
IO_LOC  "pmod[1]"  86;   // TXS A1 -> B1
IO_LOC  "pmod[2]"  84;   // TXS A3 -> B3
IO_LOC  "pmod[3]"  82;   // TXS A5 -> B5
IO_LOC  "pmod[4]"  80;   // TXS A7 -> B7
IO_LOC  "pmod[7]"  85;   // TXS A2 -> B2
IO_LOC  "pmod[8]"  83;   // TXS A4 -> B4
IO_LOC  "pmod[9]"  81;   // TXS A6 -> B6
IO_LOC  "pmod[10]" 79;   // TXS A8 -> B8

IO_PORT "pmod[1]"  IO_TYPE=LVCMOS18 PULL_MODE=NONE DRIVE=8;
IO_PORT "pmod[2]"  IO_TYPE=LVCMOS18 PULL_MODE=NONE DRIVE=8;
IO_PORT "pmod[3]"  IO_TYPE=LVCMOS18 PULL_MODE=NONE DRIVE=8;
IO_PORT "pmod[4]"  IO_TYPE=LVCMOS18 PULL_MODE=NONE DRIVE=8;
IO_PORT "pmod[7]"  IO_TYPE=LVCMOS18 PULL_MODE=NONE DRIVE=8;
IO_PORT "pmod[8]"  IO_TYPE=LVCMOS18 PULL_MODE=NONE DRIVE=8;
IO_PORT "pmod[9]"  IO_TYPE=LVCMOS18 PULL_MODE=NONE DRIVE=8;
IO_PORT "pmod[10]" IO_TYPE=LVCMOS18 PULL_MODE=NONE DRIVE=8;


// ---------------------------------------------------------------------------
// Optional: Tang onboard HDMI (pins 68-75 are not routed on the shield)
// Use with ELVDS_OBUF / TLVDS_OBUF in HDL; constrain only the _p port.
// ---------------------------------------------------------------------------
// IO_LOC  "tmds_clk_p"  69,68;
// IO_LOC  "tmds_d_p[0]" 71,70;
// IO_LOC  "tmds_d_p[1]" 73,72;
// IO_LOC  "tmds_d_p[2]" 75,74;
// IO_PORT "tmds_clk_p"  IO_TYPE=LVCMOS33D PULL_MODE=NONE DRIVE=8;
// IO_PORT "tmds_d_p[0]" IO_TYPE=LVCMOS33D PULL_MODE=NONE DRIVE=8;
// IO_PORT "tmds_d_p[1]" IO_TYPE=LVCMOS33D PULL_MODE=NONE DRIVE=8;
// IO_PORT "tmds_d_p[2]" IO_TYPE=LVCMOS33D PULL_MODE=NONE DRIVE=8;

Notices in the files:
hardware/tang-nano-9k-shield.kicad_pcb:
© Stylt 2026
